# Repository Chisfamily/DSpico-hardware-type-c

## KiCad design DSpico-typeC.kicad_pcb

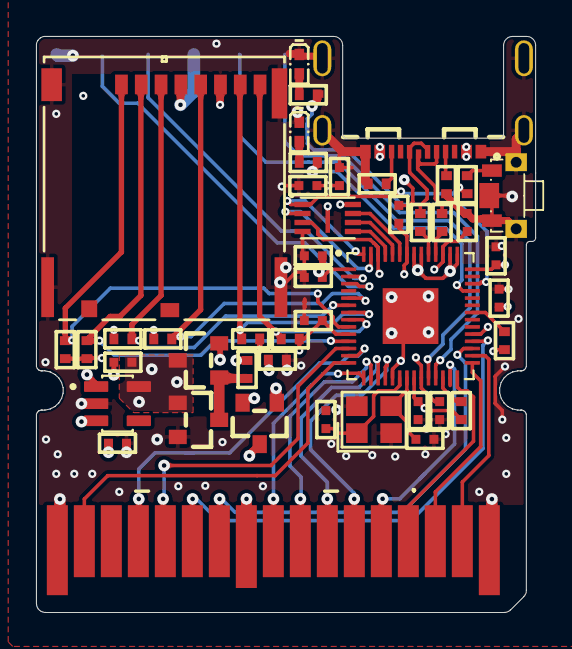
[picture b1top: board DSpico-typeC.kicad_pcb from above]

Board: 4 copper layers, 27.7 x 32.0 mm, 46 parts (1 on the bottom side), 51 nets.

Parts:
C1, C2, C3, C9: 1uF; C0402
C4, C5, C6, C7, C8, C10, C11, C15: 100NF; C0402
C12, C13: 12PF; C0402
C14: 2.2uF; C0402
D1: BL-HB337A-AV-TRB; LED0402-RD
D2: BL-HUB37A-AV-TRB; LED0402-RD
J1: 5033981892; 503398-1892_MOL
J2: USB_C_Receptacle_USB2.0_16P; USB-C-SMD_TYPE-C-16P-CB0.8-073
J3: NDS_CARDA; NDS_CARD
J4: DSPICO-DEV-PORT; EP_DEV_PORT
Q1, Q2: SI2307CDS-T1-E3; SOT-23_L2.9-W1.3-P1.90-LS2.4-BR
Q3: 2N7002KQ-7; SOT-23_L2.9-W1.3-P1.90-LS2.4-BR
R1, R2: 100K; R0402
R3, R4, R5, R6, R7, R8, R9: 10K; R0402
R10, R11: RC0402FR-0727RL; R0402
R12: 120R; R0402
R13: 220R; R0402
R14, R15: 1K; R0402
R16, R17: 5.1K; R0402
S1: SKTDLDE010; KEY-SMD_SKTDLDE010
U1: AP2112K-3.3TRG1; SOT95P285X140-5N
U2: RP2040; QFN40P700X700X90-57N
U3: W25Q16JVUXIQ; SON50P300X200X60-9N
X1: XYDBPCNANF-12MHZ; OSC-SMD_4P-L2.5-W2.0-BL

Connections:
+1V1: C9.2, C10.2, C11.2, U2.23 (DVDD), U2.45 (VREG_VOUT), U2.50 (DVDD)
+3V3: C3.2, C4.2, C5.2, C6.2, C7.2, C8.2, C14.2, C15.2, J1.4 (VDD), J4.3 (3V3), Q1.2 (S), Q2.2 (S), R2.2, R3.2, R4.2, R5.2, R6.2, R7.2, R8.2, R9.2, U2.1 (IOVDD), U2.10 (IOVDD), U2.22 (IOVDD), U2.33 (IOVDD), U2.42 (IOVDD), U2.43 (ADC_AVDD), U2.44 (VREG_VIN), U2.48 (USB_VDD), U2.49 (IOVDD), U3.8 (VCC)
+3V3_BUS: C2.2, Q1.1 (G), Q2.3 (D), Q3.1 (G), R1.1, R15.1, U1.5 (VOUT)
+3V3_DS: J3.8 (VCC), Q1.3 (D)
+VBUS: C1.2, J2.A4B9 (VBUS), J2.B4A9 (VBUS), U1.1 (VIN), U1.3 (EN)
/CLK_DS: J3.2 (CLK), U2.14 (GPIO11)
/CLK_SD: J1.5 (CLK), R9.1, U2.5 (GPIO3)
/CMD: J1.3 (CMD), R4.1, U2.6 (GPIO4)
/D0: J3.9 (D0), U2.15 (GPIO12)
/D1: J3.10 (D1), U2.16 (GPIO13)
/D2: J3.11 (D2), U2.17 (GPIO14)
/D3: J3.12 (D3), U2.18 (GPIO15)
/D4: J3.13 (D4), U2.27 (GPIO16)
/D5: J3.14 (D5), U2.28 (GPIO17)
/D6: J3.15 (D6), U2.29 (GPIO18)
/D7: J3.16 (D7), U2.30 (GPIO19)
/DAT0: J1.7 (DAT0), R8.1, U2.7 (GPIO5)
/DAT1: J1.8 (DAT1), R7.1, U2.8 (GPIO6)
/DAT2: J1.1 (DAT2), R6.1, U2.9 (GPIO7)
/DAT3: J1.2 (DAT3/CD), R5.1, U2.11 (GPIO8)
/D_N: J2.A7 (D-), J2.B7 (D-), R10.1
/D_P: J2.A6 (D+), J2.B6 (D+), R11.1
/IRQ: J3.7 (IRQ), U2.31 (GPIO20)
/LED_B: R12.2, U2.40 (GPIO28/ADC2)
/LED_R: R13.2, U2.39 (GPIO27/ADC1)
/QSPI_SCLK: U2.52 (QSPI_SCLK), U3.6 (CLK)
/QSPI_SD0: U2.53 (QSPI_SD0), U3.5 (DI_(IO0))
/QSPI_SD1: U2.55 (QSPI_SD1), U3.2 (DO_(IO1))
/QSPI_SD2: U2.54 (QSPI_SD2), U3.3 (~WP_(IO2))
/QSPI_SD3: U2.51 (QSPI_SD3), U3.7 (~HOLD_(IO3))
/QSPI_SS: R14.2, U2.56 (QSPI_CSN), U3.1 (~CS)
/ROM_CS: J3.4 (ROM_CS), U2.13 (GPIO10)
/RST_DS: J3.5 (RESET), U2.12 (GPIO9)
/SPI_CS: J3.6 (EEPROM_CS), U2.32 (GPIO21)
/SWCLK: J4.2 (SWCLK), U2.24 (SWCLK)
/SWD: J4.1 (SWD), U2.25 (SWD)
/UART_RX: J4.5 (RX), U2.3 (GPIO1)
/UART_TX: J4.4 (TX), U2.2 (GPIO0)
/USB_D_N: R10.2, U2.46 (USB_DM)
/USB_D_P: R11.2, U2.47 (USB_DP)
GND: C1.1, C2.1, C3.1, C4.1, C5.1, C6.1, C7.1, C8.1, C9.1, C10.1, C11.1, C12.1, C13.1, C14.1, C15.1, D1.1, D2.1, J1.6 (VSS), J1.11 (SHD), J1.12 (SHD), J1.13 (SHD), J1.14 (SHD), J2.A1B12 (GND), J2.B1A12 (GND), J2.S1 (SHIELD), J3.1 (GND), J3.17 (GND), J4.6 (GND), Q3.2 (S), R1.2, R16.2, R17.2, S1.1, S1.3, S1.4, U1.2 (GND), U2.19 (TESTEN), U2.57 (GND), U3.4 (GND), U3.9 (EP), X1.2, X1.4
unnamed: D1.2, R12.1
unnamed: D2.2, R13.1
unnamed: J2.A5 (CC1), R16.1
unnamed: J2.B5 (CC2), R17.1
unnamed: Q2.1 (G), Q3.3 (D), R2.1
unnamed: R14.1, S1.2
unnamed: R15.2, U2.36 (GPIO24)
unnamed: R3.1, U2.26 (RUN)
unnamed: C12.2, U2.20 (XIN), X1.1
unnamed: C13.2, U2.21 (XOUT), X1.3

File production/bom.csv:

Designator,Footprint,Quantity,Value,LCSC Part #
"C1, C2, C3, C9",C0402,4,1uF,
"C10, C11, C15, C4, C5, C6, C7, C8",C0402,8,100NF,
"C12, C13",C0402,2,12PF,
C14,C0402,1,2.2uF,
D1,LED0402-RD,1,BL-HB337A-AV-TRB,
D2,LED0402-RD,1,BL-HUB37A-AV-TRB,
J1,503398-1892_MOL,1,5033981892,
J2,USB-C-SMD_TYPE-C-16P-CB0.8-073,1,USB_C_Receptacle_USB2.0_16P,
J3,NDS_CARD,1,NDS_CARDA,
J4,EP_DEV_PORT,1,DSPICO-DEV-PORT,
"Q1, Q2",SOT-23_L2.9-W1.3-P1.90-LS2.4-BR,2,SI2307CDS-T1-E3,
Q3,SOT-23_L2.9-W1.3-P1.90-LS2.4-BR,1,2N7002KQ-7,
"R1, R2",R0402,2,100K,
"R10, R11",R0402,2,RC0402FR-0727RL,
R12,R0402,1,120R,
R13,R0402,1,220R,
"R14, R15",R0402,2,1K,
"R16, R17",R0402,2,5.1K,
"R3, R4, R5, R6, R7, R8, R9",R0402,7,10K,
S1,KEY-SMD_SKTDLDE010,1,SKTDLDE010,
U1,SOT95P285X140-5N,1,AP2112K-3.3TRG1,
U2,QFN40P700X700X90-57N,1,RP2040,
U3,SON50P300X200X60-9N,1,W25Q16JVUXIQ,
X1,OSC-SMD_4P-L2.5-W2.0-BL,1,XYDBPCNANF-12MHZ,
